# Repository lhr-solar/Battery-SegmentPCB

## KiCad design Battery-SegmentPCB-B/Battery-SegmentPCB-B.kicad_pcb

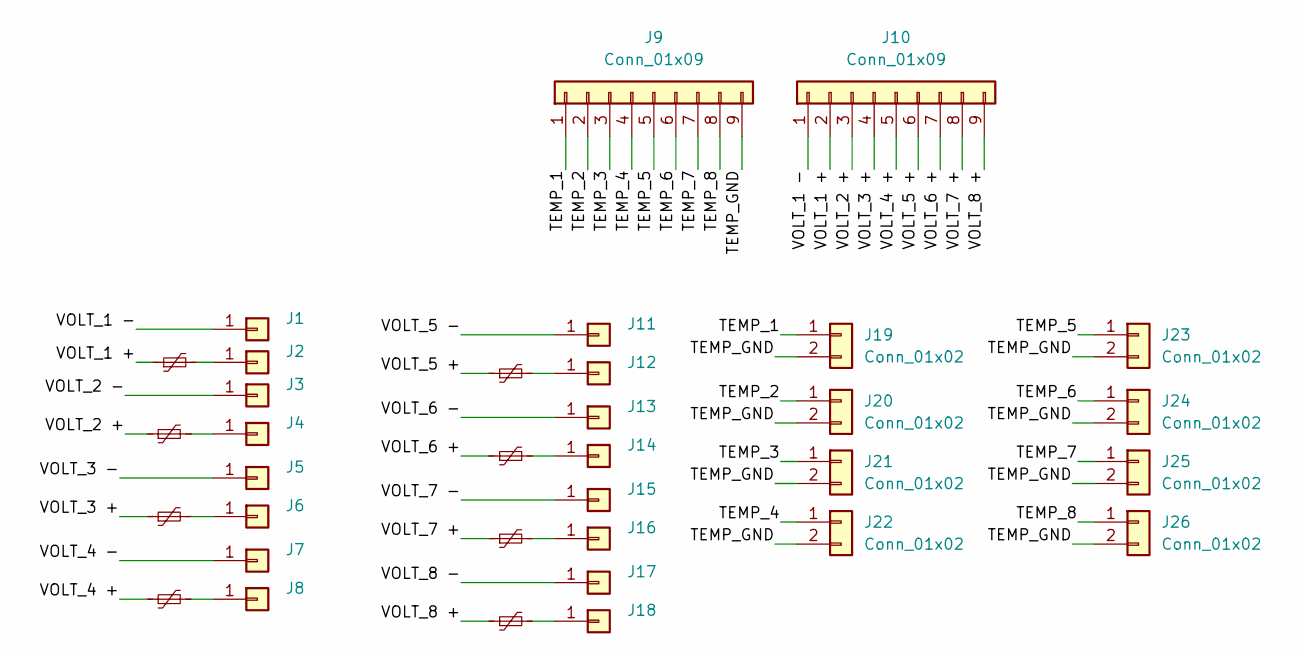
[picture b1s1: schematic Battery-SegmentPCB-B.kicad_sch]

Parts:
F37, F38, F39, F40, F41, F42, F43, F44: PTC Fuse; FUSC1810X100N
J1, J2, J3, J4, J5, J6, J7, J8, J11, J12, J13, J14, J15, J16, J17, J18: Conn_01x01; MountingHole_3.2mm_M3_DIN965_Pad_TopOnly
J9, J10: Conn_01x09; CON_436500915_MOL
J19, J20, J21, J22, J23, J24, J25, J26: Conn_01x02; 105313-2102

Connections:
/TEMP_1: J9.1, J19.1
/TEMP_2: J9.2, J20.1
/TEMP_3: J9.3, J21.1
/TEMP_4: J9.4, J22.1
/TEMP_5: J9.5, J23.1
/TEMP_6: J9.6, J24.1
/TEMP_7: J9.7, J25.1
/TEMP_8: J9.8, J26.1
/TEMP_GND: J9.9, J19.2, J20.2, J21.2, J22.2, J23.2, J24.2, J25.2, J26.2
/VOLT_1 +: F37.1, J10.2
/VOLT_1 -: J1.1, J10.1
/VOLT_2 +: F38.1, J10.3
/VOLT_2 -: J3.1
/VOLT_3 +: F39.1, J10.4
/VOLT_3 -: J5.1
/VOLT_4 +: F40.1, J10.5
/VOLT_4 -: J7.1
/VOLT_5 +: F44.1, J10.6
/VOLT_5 -: J11.1
/VOLT_6 +: F43.1, J10.7
/VOLT_6 -: J13.1
/VOLT_7 +: F42.1, J10.8
/VOLT_7 -: J15.1
/VOLT_8 +: F41.1, J10.9
/VOLT_8 -: J17.1
unnamed: F37.2, J2.1
unnamed: F38.2, J4.1
unnamed: F39.2, J6.1
unnamed: F40.2, J8.1
unnamed: F44.2, J12.1
unnamed: F43.2, J14.1
unnamed: F42.2, J16.1
unnamed: F41.2, J18.1

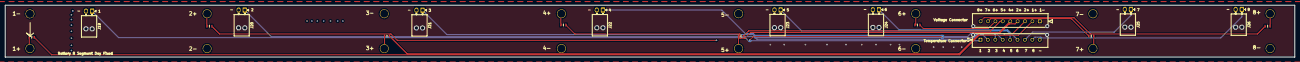
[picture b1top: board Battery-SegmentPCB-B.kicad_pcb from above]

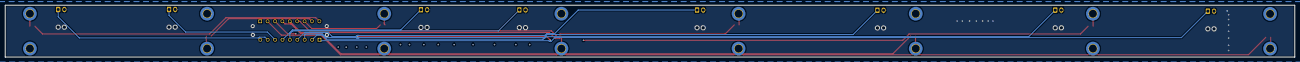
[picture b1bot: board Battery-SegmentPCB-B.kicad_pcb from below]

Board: 4 copper layers, 522.7 x 21.0 mm, 34 parts (16 on the bottom side), 26 nets.

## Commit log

2024-10-05 Update .gitignore
    added .ick
2024-10-05 updated boards
2024-10-12 I updated PcbB to PCBV2
2024-10-22 new template
2025-03-10 started
2025-03-19 womp womp(done)
2025-04-01 FUCK I FORGOT B
2025-04-01 fuck
2025-04-01 forgot to remove one of the designiators
2025-04-17 b done
2025-04-17 stuff
2025-04-17 done?
2025-06-17 seg A, 4 layer, moved conns, flipped fuses, fixed labels
2025-06-17 seg B 4 layer
2025-06-17 removed traces
2025-06-18 redid A
2025-06-18 redid b
